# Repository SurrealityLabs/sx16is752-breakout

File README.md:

# sc16is752-breakout
A breakout board for the SC16IS752 I2C/SPI-to-dual-UART IC

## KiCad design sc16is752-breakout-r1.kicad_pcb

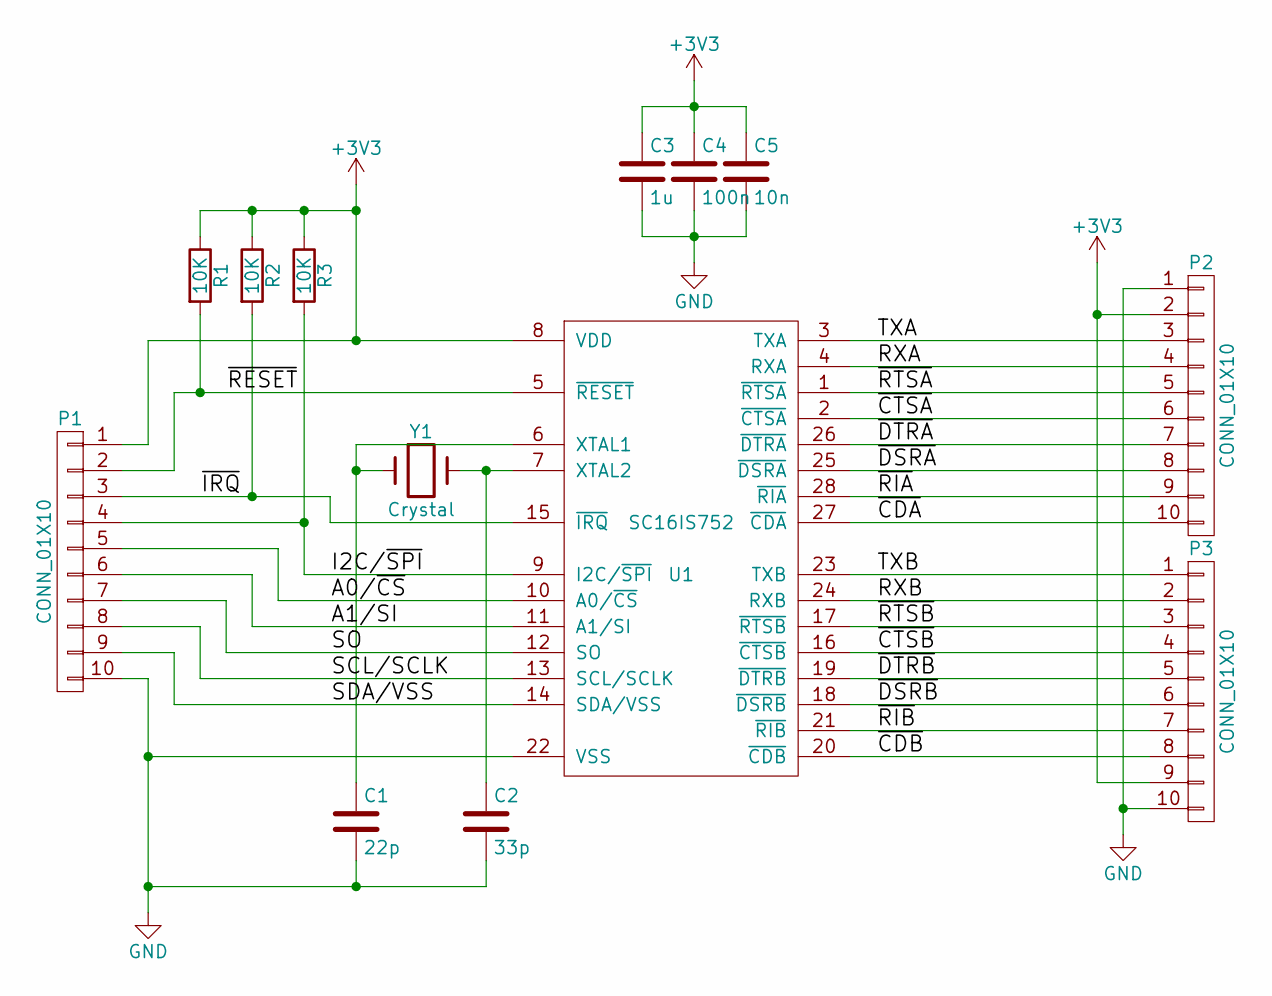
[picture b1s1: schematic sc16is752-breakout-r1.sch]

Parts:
C1: 22p; C_0603
C2: 33p; C_0603
C3: 1u; C_0603
C4: 100n; C_0603
C5: 10n; C_0603
P1, P2, P3: CONN_01X10; Pin_Header_Straight_1x10
R1, R2, R3: 10K; R_0603
U1: SC16IS752; TSSOP-28_4.4x9.7mm_Pitch0.65mm
Y1: Crystal; Crystal_HC49-SD_SMD

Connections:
+3V3: C3.1, C4.1, C5.1, P1.1, P2.2, P3.9, R1.1, R2.1, R3.1, U1.8 (VDD)
/A0/~CS: P1.5, U1.10 (A0/~CS)
/A1/SI: P1.6, U1.11 (A1/SI)
/I2C/~SPI: P1.4, R3.2, U1.9 (I2C/~SPI)
/RXA: P2.4, U1.4 (RXA)
/RXB: P3.2, U1.24 (RXB)
/SCL/SCLK: P1.8, U1.13 (SCL/SCLK)
/SDA/VSS: P1.9, U1.14 (SDA/VSS)
/SO: P1.7, U1.12 (SO)
/TXA: P2.3, U1.3 (TXA)
/TXB: P3.1, U1.23 (TXB)
/~CDA: P2.10, U1.27 (~CDA)
/~CDB: P3.8, U1.20 (~CDB)
/~CTSA: P2.6, U1.2 (~CTSA)
/~CTSB: P3.4, U1.16 (~CTSB)
/~DSRA: P2.8, U1.25 (~DSRA)
/~DSRB: P3.6, U1.18 (~DSRB)
/~DTRA: P2.7, U1.26 (~DTRA)
/~DTRB: P3.5, U1.19 (~DTRB)
/~IRQ: P1.3, R2.2, U1.15 (~IRQ)
/~RESET: P1.2, R1.2, U1.5 (~RESET)
/~RIA: P2.9, U1.28 (~RIA)
/~RIB: P3.7, U1.21 (~RIB)
/~RTSA: P2.5, U1.1 (~RTSA)
/~RTSB: P3.3, U1.17 (~RTSB)
GND: C1.2, C2.2, C3.2, C4.2, C5.2, P1.10, P2.1, P3.10, U1.22 (VSS)
unnamed: C1.1, U1.6 (XTAL1), Y1.1
unnamed: C2.1, U1.7 (XTAL2), Y1.2

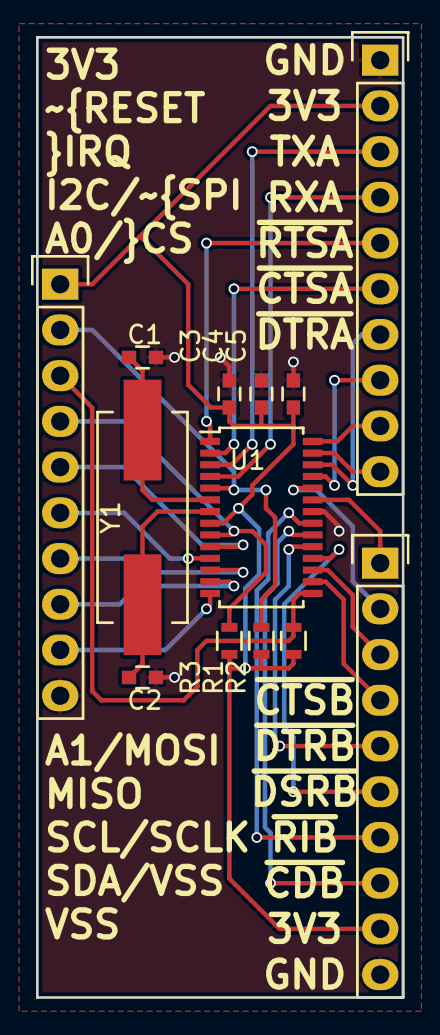
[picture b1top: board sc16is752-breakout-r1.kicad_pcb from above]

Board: 2 copper layers, 20.3 x 53.3 mm, 13 parts (0 on the bottom side), 28 nets.

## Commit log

2016-09-08 Initial import
